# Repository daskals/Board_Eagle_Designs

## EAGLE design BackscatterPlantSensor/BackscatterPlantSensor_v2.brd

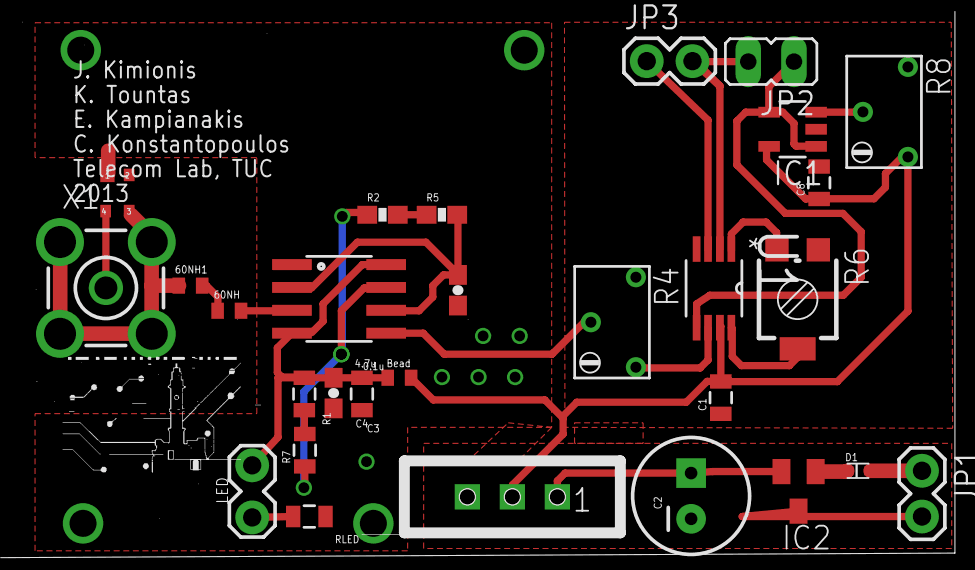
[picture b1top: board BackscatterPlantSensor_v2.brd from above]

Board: 2 copper layers, 29 parts (0 on the bottom side), 25 nets.

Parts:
60NH, 60NH1: C0402
C1, C8: 10uF; 0805
C2: CPOL-RADIAL-100UF-25V
C3: 0.1u; 0603-CAP
C4: 4.7u; 0805
C5: 0; 0603-CAP
D1: SOD523
IC1: MCP601OT; SOT23-5
IC2: MAX6520; SOT23
JP1, JP3: 1X02
JP2: JP1
L1: Bead; C0402
LED: LED; 1X02_LOCK
R1, R7: 0805
R2, R5: 0603-RES
R4, R8: RTRIM74W
R6: RTRIM3314G
RLED: 0805
U1: INA326EA/250; SOP65P490X110-8N
U$1: DS1307SO8; SO08
U$2: SPDT-SLIDE-1218
U$3: BF1118SOT343R_NXP; SOT343R
X1: BU-SMA-V

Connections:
AGND: C1.1, C8.2, IC1.2, R4.1, R8.1, U1.4
DGND: C3.2, C4.2, C5.2, RLED.2, U$1.1, U$3.1
DRAIN: U$3.4, X1.1
FOUT: 60NH.2, U$1.3
FOUT2: 60NH1.1, U$3.3, X1.2
GND: C2.2, IC2.3, JP1.2, X1.3, X1.4, X1.5
IN: D1.C, IC2.1
unnamed: 60NH.1, 60NH1.2
unnamed: LED.2, RLED.1
unnamed: IC1.3, R8.2
unnamed: JP2.2, JP3.2, U1.2
unnamed: JP3.1, U1.3
unnamed: R6.2, U1.8
unnamed: R6.1, U1.1
unnamed: D1.A, JP1.1
unnamed: R1.1, R7.2
unnamed: R2.2, R5.1
P6: C5.1, R5.2, U$1.2, U$1.6
P7: R2.1, R7.1, U$1.7
POWER: C2.1, IC2.2, U$2.P1
POWEROUT: C1.2, C8.1, IC1.5, L1.1, R8.3, U1.7, U$2.P2
VDD: C3.1, C4.1, L1.2, LED.1, R1.2, U$1.4, U$1.8
VOUT1: R4.2, U$1.5
VOUT12: R4.3, U1.6
VREF: IC1.1, IC1.4, JP2.1, U1.5

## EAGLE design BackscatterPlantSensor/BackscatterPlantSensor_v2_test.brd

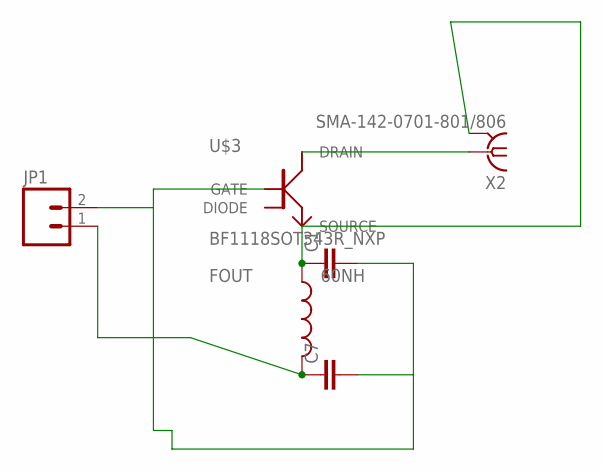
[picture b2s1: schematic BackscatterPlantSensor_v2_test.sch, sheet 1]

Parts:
60NH: INDUCTOR0402; C0402
C1, C7: CAP0402-CAP; 0402-CAP
JP1: M02PTH; 1X02
U$3: BF1118SOT343R_NXP; SOT343R
X2: SMA-142-0701-801/806; J502-ND-142-0701-801/806

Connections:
DGND: C1.2, C7.2, JP1.2, U$3.1 (GATE)
DRAIN: U$3.4 (DRAIN), X2.1
FOUT: 60NH.2, C7.1, JP1.1
FOUT2: 60NH.1, C1.1, U$3.3 (SOURCE), X2.G@1 (GND)
GND: X2.G@2 (GND), X2.G@3 (GND), X2.G@4 (GND)

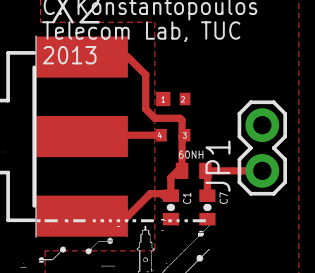
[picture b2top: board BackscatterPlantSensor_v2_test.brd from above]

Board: 2 copper layers, 6 parts (0 on the bottom side), 5 nets.

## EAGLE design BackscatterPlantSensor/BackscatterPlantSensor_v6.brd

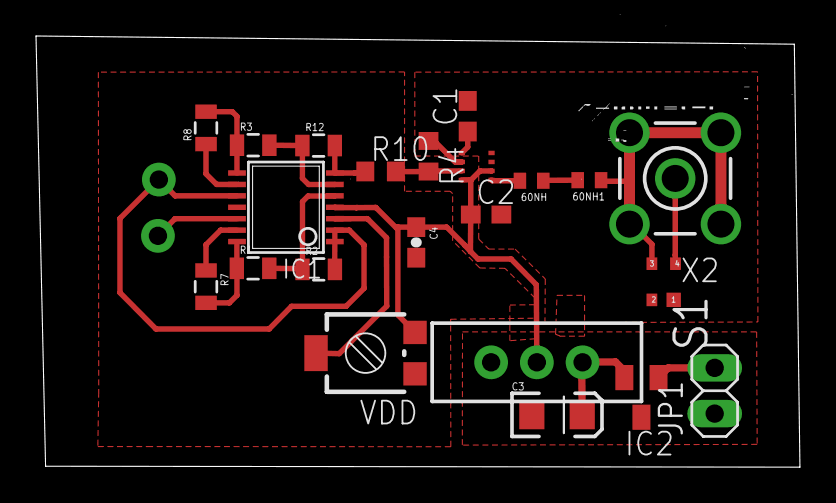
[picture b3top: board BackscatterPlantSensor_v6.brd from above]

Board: 2 copper layers, 42.4 x 24.0 mm, 24 parts (0 on the bottom side), 22 nets.

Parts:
60NH, 60NH1: C0402
C1, C2: C0603
C3: EIA3216
C4: 0603-CAP
IC1: MCP604ST; TSSOP14
IC2: MAX6520; SOT23
JP1: 1X02
R1, R2, R3, R12: 100K; 0805
R4, R10: R0603
R7, R8: 50K; 0805
S1: SWITCH-SPDT
U$1: TDFN22-8
U$4: BF1118SOT343R_NXP; SOT343R
V+: M01SMDNS; 1X01NS
V-: M01SMDNS; 1X01NS
VDD: RTRIM3314G
X2: LTI-SASF54GT

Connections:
AGND: C4.2, IC1.11, VDD.3
DGND: C1.2, C2.2, R4.1, U$1.4, U$1.6, U$4.1
DRAIN: U$4.4, X2.1
FOUT: 60NH.2, U$1.1
FOUT2: 60NH1.1, U$4.3, X2.2
GND: C3.C, IC2.3, JP1.1, X2.3, X2.4, X2.5
unnamed: C1.1, U$1.5
unnamed: R4.2, R10.2, U$1.7
unnamed: 60NH.1, 60NH1.2
unnamed: IC2.1, JP1.2
unnamed: C3.A, IC2.2, S1.1
unnamed: IC1.3, VDD.2
unnamed: IC1.13, R7.1
unnamed: IC1.5, R1.2, R2.1
unnamed: IC1.9, R8.1
unnamed: IC1.8, R3.1, R8.2
unnamed: IC1.14, R1.1, R7.2
unnamed: IC1.6, R3.2, R12.1
V+: IC1.12, V+.1
VCOND: IC1.7, R10.1, R12.2
VDD: C2.1, C4.1, IC1.4, S1.2, U$1.2, U$1.8, VDD.1
VRF: IC1.1, IC1.2, IC1.10, R2.2, V-.1

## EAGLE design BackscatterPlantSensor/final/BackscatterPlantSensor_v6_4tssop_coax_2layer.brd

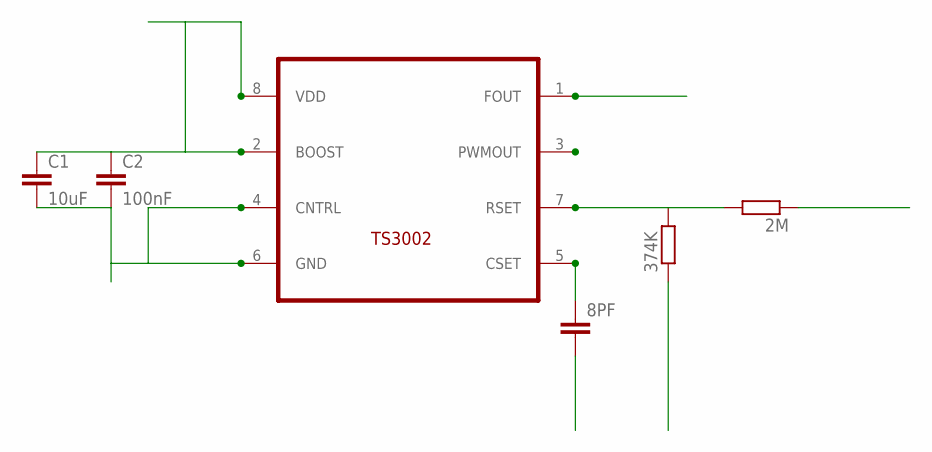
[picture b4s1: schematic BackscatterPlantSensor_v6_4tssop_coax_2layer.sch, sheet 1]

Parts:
2M, 374K: R-EU_R0603; R0603
8PF: CC0603; C0603
C1: 10uF; C0603
C2: 100nF; C0603
U$1: TS3002; TDFN22-8

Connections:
AGND: 374K.1; also elsewhere on the board
DGND: 8PF.2, C1.2, C2.2, U$1.4 (CNTRL), U$1.6 (GND); also elsewhere on the board
FOUT: U$1.1 (FOUT); also elsewhere on the board
unnamed: 8PF.1, U$1.5 (CSET)
unnamed: 2M.2, 374K.2, U$1.7 (RSET)
VCOND1: 2M.1; also elsewhere on the board
VDD: C1.1, C2.1, U$1.2 (BOOST), U$1.8 (VDD); also elsewhere on the board

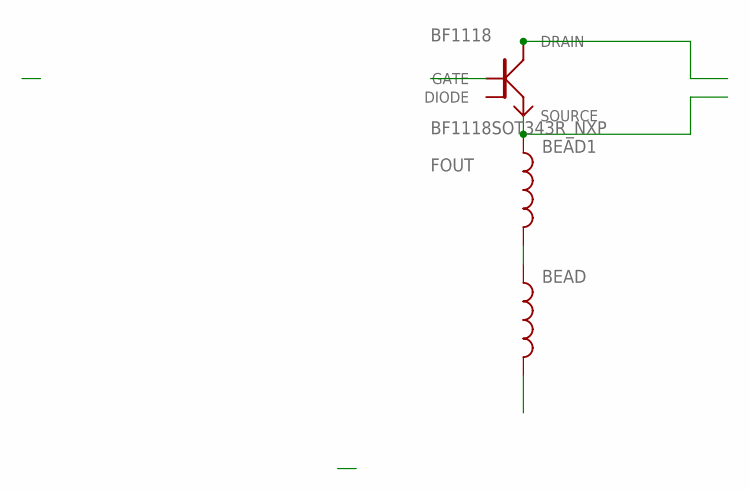
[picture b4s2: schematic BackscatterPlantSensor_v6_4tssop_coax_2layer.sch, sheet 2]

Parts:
BEAD, BEAD1: INDUCTOR0402; C0402
BF1118: BF1118SOT343R_NXP; SOT343R

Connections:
DGND: BF1118.1 (GATE); also elsewhere on the board
FOUT: BEAD.2; also elsewhere on the board
unnamed: BEAD.1, BEAD1.2
RF_MINUS: BEAD1.1, BF1118.3 (SOURCE)
RF_PLUS: BF1118.4 (DRAIN)

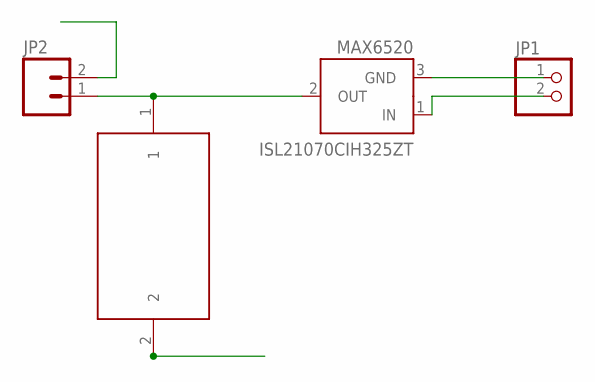
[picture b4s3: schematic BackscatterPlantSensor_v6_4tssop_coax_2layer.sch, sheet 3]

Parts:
ISL21070CIH325ZT: MAX6520; SOT23
JP1: PINHD-1X2; 1X02
JP2: M02PTH; 1X02
U$2: RVB0E221MNG; CAP_ELECTROLYTIC

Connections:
220UF: ISL21070CIH325ZT.2 (OUT), JP2.1, U$2.1
GND: ISL21070CIH325ZT.3 (GND), JP1.1, U$2.2
unnamed: ISL21070CIH325ZT.1 (IN), JP1.2
VDD: JP2.2; also elsewhere on the board

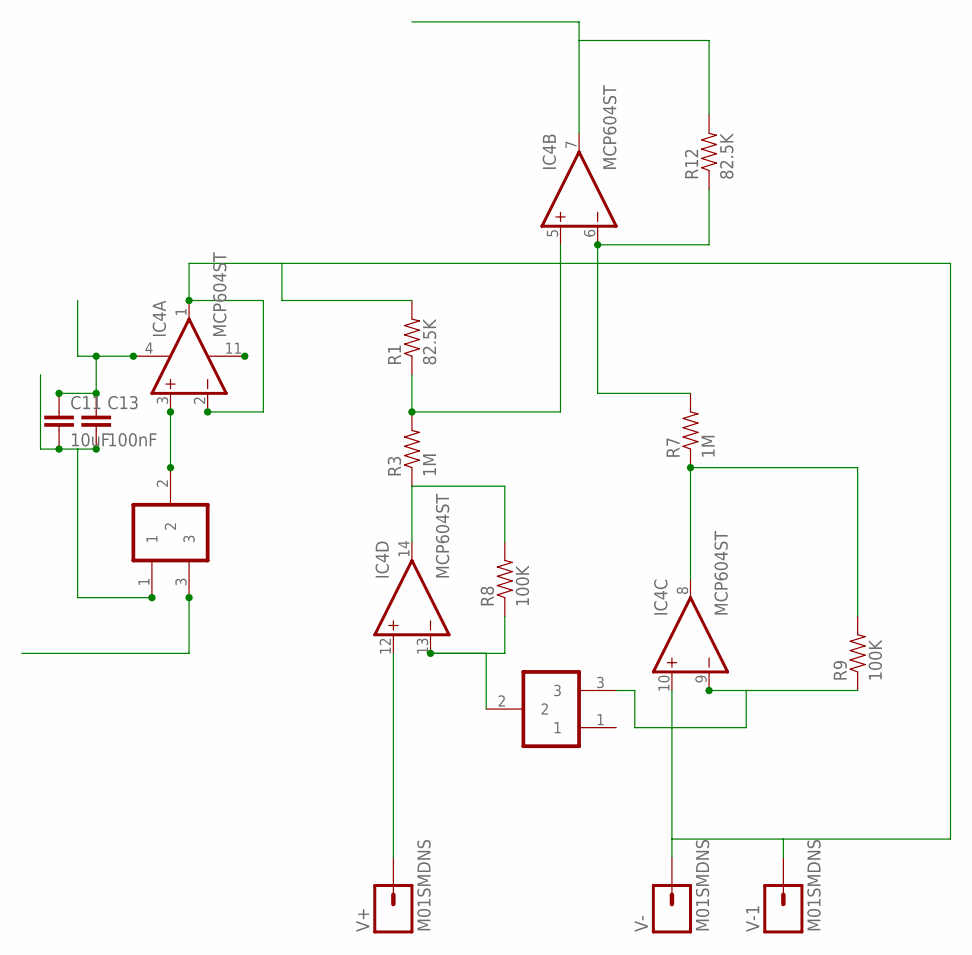
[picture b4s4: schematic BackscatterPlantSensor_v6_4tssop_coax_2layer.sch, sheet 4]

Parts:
C11: 10uF; 0603-CAP
C13: 100nF; 0603-CAP
IC4: MCP604ST; TSSOP14
R1, R12: 82.5K; 0805
R3, R7: 1M; 0805
R8, R9: 100K; 0805
TRIMMER2.2K: MURATA_PVA2A225; PVATRIMMER
U$5: MURATA_PVA2A225; PVATRIMMER
V+: M01SMDNS; 1X01NS
V-, V-1: M01SMDNS; 1X01NS

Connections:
AGND: C11.2, C13.2, IC4.11 (V-), U$5.1; also elsewhere on the board
unnamed: IC4.13 (-IN), R8.1, TRIMMER2.2K.2
unnamed: IC4.9 (-IN), R9.1, TRIMMER2.2K.3
unnamed: IC4.8 (OUT), R7.1, R9.2
unnamed: IC4.14 (OUT), R3.1, R8.2
unnamed: IC4.6 (-IN), R7.2, R12.1
unnamed: IC4.3 (+IN), U$5.2
unnamed: IC4.5 (+IN), R1.1, R3.2
V+: IC4.12 (+IN), V+.1
VCOND1: IC4.7 (OUT), R12.2; also elsewhere on the board
VDD: C11.1, C13.1, IC4.4 (V+), U$5.3; also elsewhere on the board
VRF: IC4.1 (OUT), IC4.2 (-IN), IC4.10 (+IN), R1.2, V-.1, V-1.1

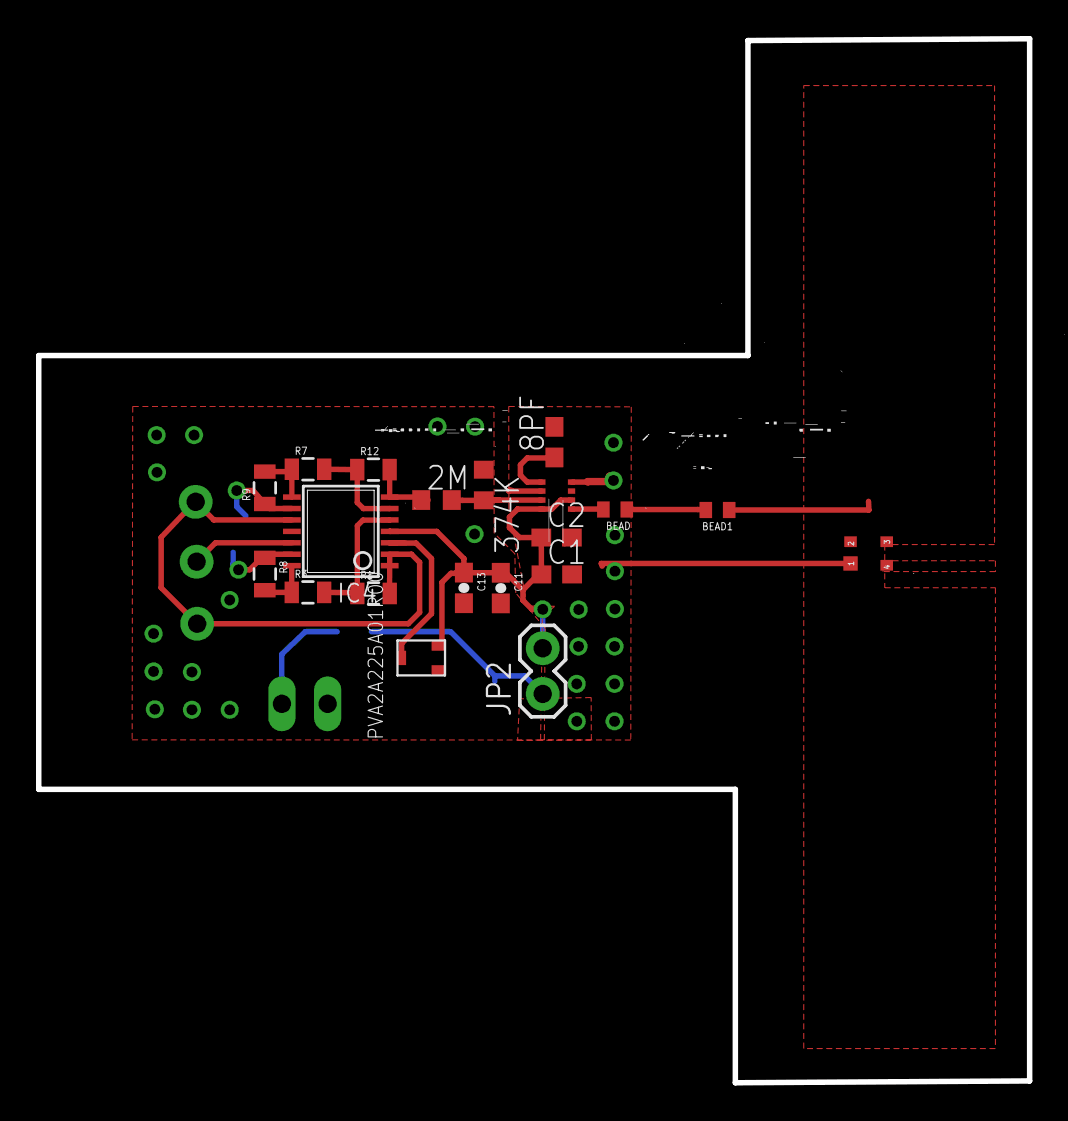
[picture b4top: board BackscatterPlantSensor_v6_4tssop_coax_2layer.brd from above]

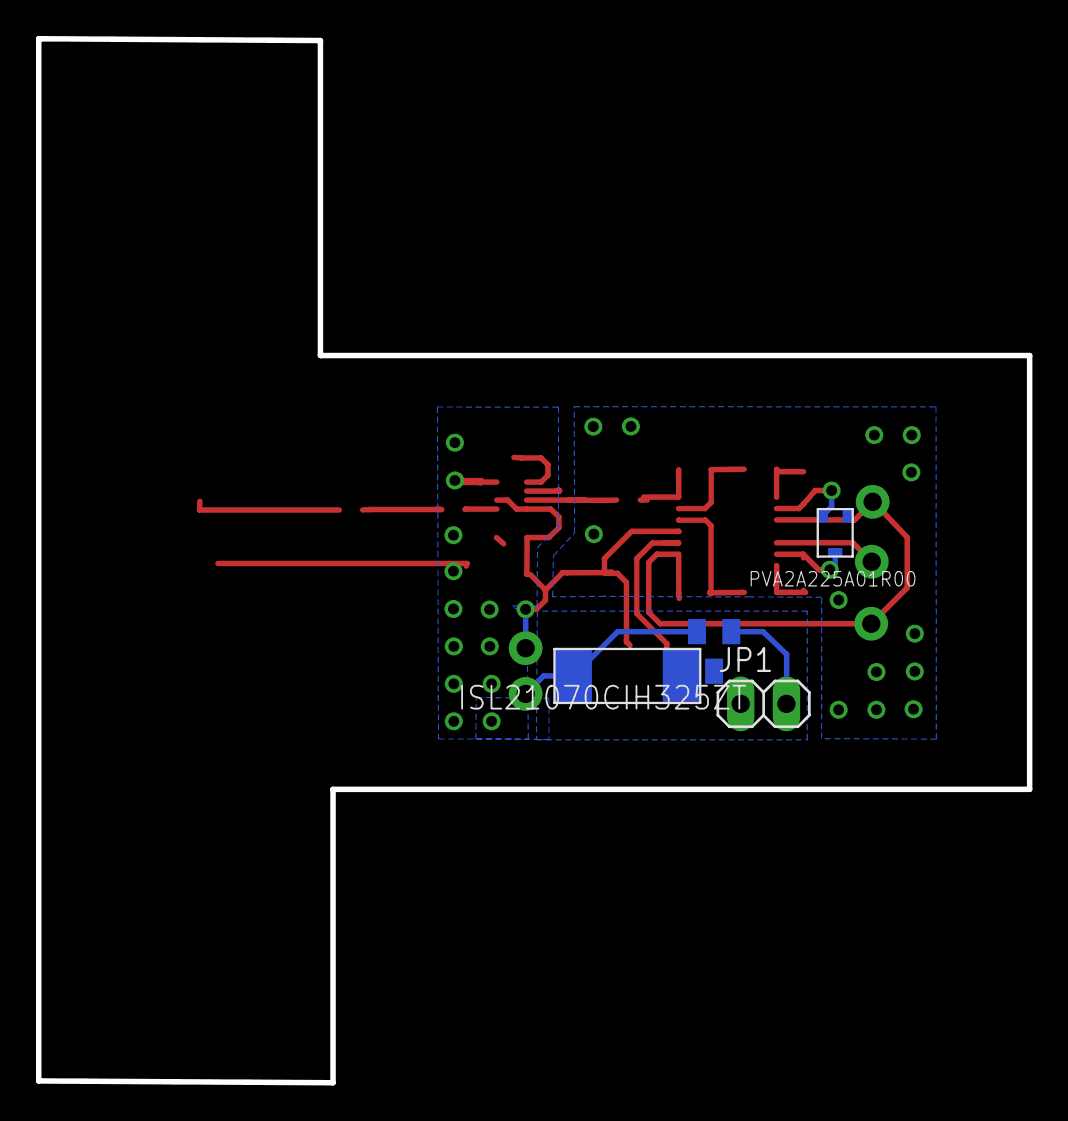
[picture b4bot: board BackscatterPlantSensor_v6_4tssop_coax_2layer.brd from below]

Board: 2 copper layers, 55.0 x 58.0 mm, 27 parts (4 on the bottom side), 21 nets.

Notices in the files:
parts and their libraries:
SparkFun-Resistors: Licensing: CC v3.0 Share-Alike You are welcome to use this library for commercial purposes.
